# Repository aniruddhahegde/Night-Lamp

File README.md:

# Night-Lamp
It is a simple basic lamp which lights up when the surrounding is dark.I have used LDR sensor to detect darkness,a transistor,diode and a 6V power source.I designed PCB using KiCad. Related Files are uploaded above.
So what happens the LDR as soon as darkness occurs,the resistance of LDR decreases and current can pass through it.
Now almost 16mA current will flow hence 330 ohm resistor been taken.
The estimation,Bill of materials been added in the files above.
The improvement we can make is adding some sort of sound effects will make it more effective.
I honestly say,I have taken help of AI(Claude),it guided me how to complete it.
I learned so much things I didn't even knew such thing exist,but I really enjoyed and had very good experience with 
KiCad.

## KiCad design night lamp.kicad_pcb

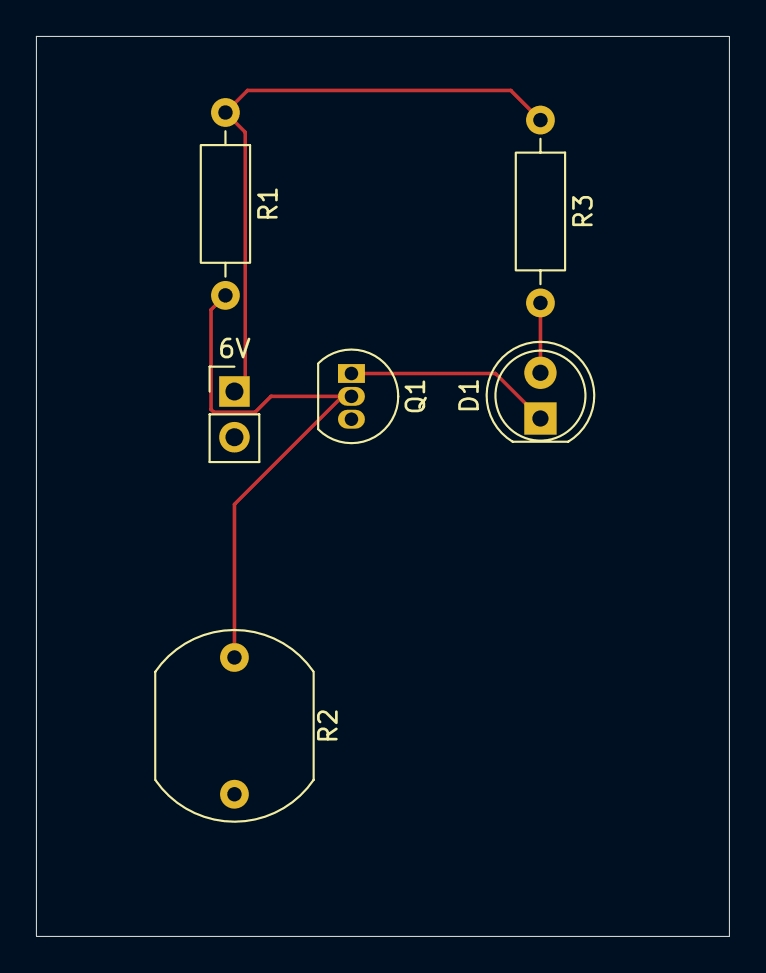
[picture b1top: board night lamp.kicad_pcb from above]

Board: 2 copper layers, 38.5 x 50.0 mm, 6 parts (0 on the bottom side), 5 nets.

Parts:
6V: GND; PinHeader_1x02_P2.54mm_Vertical
D1: LED; LED_D5.0mm
Q1: BC547; TO-92_Inline
R1: 100k; R_Axial_DIN0207_L6.3mm_D2.5mm_P10.16mm_Horizontal
R2: LDR03; R_LDR_10x8.5mm_P7.6mm_Vertical
R3: 330; R_Axial_DIN0207_L6.3mm_D2.5mm_P10.16mm_Horizontal

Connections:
/GND: 6V.2, Q1.3 (E), R2.2
/VCC: 6V.1, R1.1, R3.1
unnamed: D1.2 (A), R3.2
unnamed: D1.1 (K), Q1.1 (C)
unnamed: Q1.2 (B), R1.2, R2.1
